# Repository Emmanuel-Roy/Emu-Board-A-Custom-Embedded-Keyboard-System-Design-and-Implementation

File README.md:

# Emu-Board: A Custom Embedded Keyboard System Design and Implementation
A Custom Keyboard Designed *Almost Entirely From Scratch.

Images:

Things Designed From Scratch

  -PCB (Using KiCad and ScottoKeebs Footprint and Symbol Libraries)

  -Casing (Using Ruby to laser cut the acrylic)

  -Keyboard Matrix Firmware Code (Using KMK Firmware to do the majority of the processing.)

Components Bought:

  -77 Key Switches (Boba U4T)

  -77 1N4148 Diodes

  -Durock Plate Mounted Stabilizers

  -Raspberry Pi Pico

  -Keycaps

  -M.2 Screws and Standoffs

I used the following resources to help with this project.

  -https://matt3o.com/anatomy-of-a-keyboard/

  -http://www.keyboard-layout-editor.com/

  -http://builder.swillkb.com/

  -https://github.com/joe-scotto/scottokeebs/tree/main/Extras/ScottoKicad

  -https://www.youtube.com/watch?v=8WXpGTIbxlQ

  -https://www.youtube.com/watch?v=8WXpGTIbxlQ

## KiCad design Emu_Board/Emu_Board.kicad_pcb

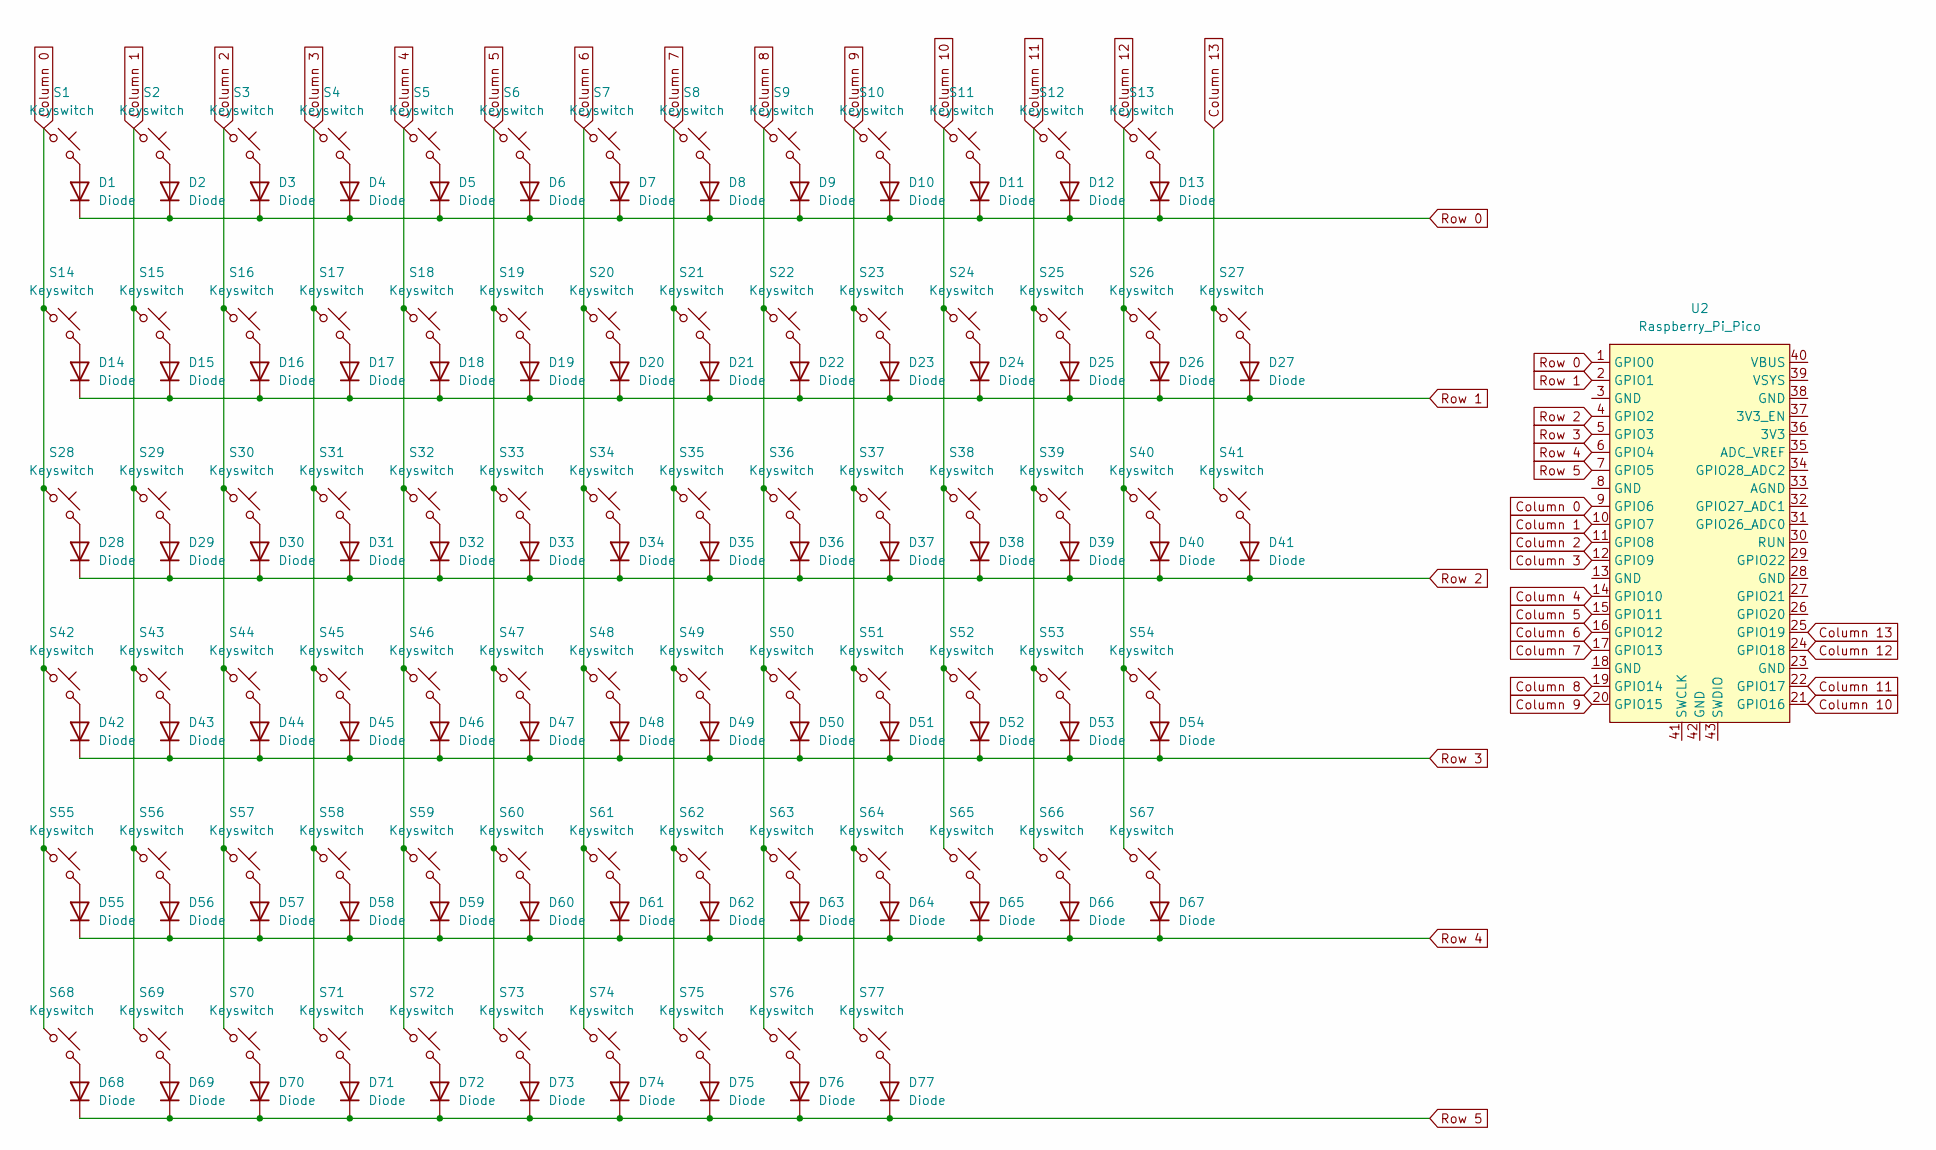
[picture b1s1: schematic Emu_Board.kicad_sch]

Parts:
D1, D2, D3, D4, D5, D6, D7, D8, D9, D10, D11, D12, D13, D14, D15, D16, D17, D18, D19, D20, D21, D22, D23, D24, D25, D26, D27, D28, D29, D30, D31, D32, D33, D34, D35, D36, D37, D38, D39, D40, D41, D42, D43, D44, D45, D46, D47, D48, D49, D50, D51, D52, D53, D54, D55, D56, D57, D58, D59, D60, D61, D62, D63, D64, D65, D66, D67, D68, D69, D70, D71, D72, D73, D74, D75, D76, D77: Diode; Diode_DO-35
S1, S2, S3, S4, S5, S6, S7, S8, S9, S10, S11, S12, S13, S14, S15, S16, S17, S18, S19, S20, S21, S22, S23, S24, S25, S26, S29, S30, S31, S32, S33, S34, S35, S36, S37, S38, S39, S40, S43, S44, S45, S46, S47, S48, S49, S50, S51, S52, S53, S56, S57, S58, S59, S60, S61, S62, S63, S64, S65, S67, S75, S76, S77: Keyswitch; MX_PCB_1.00u
S27: Keyswitch; MX_PCB_2.00u
S28, S41: Keyswitch; MX_PCB_1.50u
S42: Keyswitch; MX_PCB_1.75u
S54, S55: Keyswitch; MX_PCB_2.25u
S66: Keyswitch; MX_PCB_2.75u
S68, S69, S70, S72, S73, S74: Keyswitch; MX_PCB_1.25u
S71: Keyswitch; MX_PCB_6.25u
U2: Raspberry_Pi_Pico

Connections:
Column 0: S1.1, S14.1, S28.1, S42.1, S55.1, S68.1, U2.9 (GPIO6)
Column 1: S2.1, S15.1, S29.1, S43.1, S56.1, S69.1, U2.10 (GPIO7)
Column 2: S3.1, S16.1, S30.1, S44.1, S57.1, S70.1, U2.11 (GPIO8)
Column 3: S4.1, S17.1, S31.1, S45.1, S58.1, S71.1, U2.12 (GPIO9)
Column 4: S5.1, S18.1, S32.1, S46.1, S59.1, S72.1, U2.14 (GPIO10)
Column 5: S6.1, S19.1, S33.1, S47.1, S60.1, S73.1, U2.15 (GPIO11)
Column 6: S7.1, S20.1, S34.1, S48.1, S61.1, S74.1, U2.16 (GPIO12)
Column 7: S8.1, S21.1, S35.1, S49.1, S62.1, S75.1, U2.17 (GPIO13)
Column 8: S9.1, S22.1, S36.1, S50.1, S63.1, S76.1, U2.19 (GPIO14)
Column 9: S10.1, S23.1, S37.1, S51.1, S64.1, S77.1, U2.20 (GPIO15)
Column 10: S11.1, S24.1, S38.1, S52.1, S65.1, U2.21 (GPIO16)
Column 11: S12.1, S25.1, S39.1, S53.1, S66.1, U2.22 (GPIO17)
Column 12: S13.1, S26.1, S40.1, S54.1, S67.1, U2.24 (GPIO18)
Column 13: S27.1, S41.1, U2.25 (GPIO19)
unnamed: D1.2 (A), S1.2
unnamed: D2.2 (A), S2.2
unnamed: D3.2 (A), S3.2
unnamed: D4.2 (A), S4.2
unnamed: D5.2 (A), S5.2
unnamed: D6.2 (A), S6.2
unnamed: D7.2 (A), S7.2
unnamed: D8.2 (A), S8.2
unnamed: D9.2 (A), S9.2
unnamed: D10.2 (A), S10.2
unnamed: D11.2 (A), S11.2
unnamed: D12.2 (A), S12.2
unnamed: D13.2 (A), S13.2
unnamed: D14.2 (A), S14.2
unnamed: D15.2 (A), S15.2
unnamed: D16.2 (A), S16.2
unnamed: D17.2 (A), S17.2
unnamed: D18.2 (A), S18.2
unnamed: D19.2 (A), S19.2
unnamed: D20.2 (A), S20.2
unnamed: D21.2 (A), S21.2
unnamed: D22.2 (A), S22.2
unnamed: D23.2 (A), S23.2
unnamed: D24.2 (A), S24.2
unnamed: D25.2 (A), S25.2
unnamed: D26.2 (A), S26.2
unnamed: D27.2 (A), S27.2
unnamed: D28.2 (A), S28.2
unnamed: D29.2 (A), S29.2
unnamed: D30.2 (A), S30.2
unnamed: D31.2 (A), S31.2
unnamed: D32.2 (A), S32.2
unnamed: D33.2 (A), S33.2
unnamed: D34.2 (A), S34.2
unnamed: D35.2 (A), S35.2
unnamed: D36.2 (A), S36.2
unnamed: D37.2 (A), S37.2
unnamed: D38.2 (A), S38.2
unnamed: D39.2 (A), S39.2
unnamed: D40.2 (A), S40.2
unnamed: D41.2 (A), S41.2
unnamed: D42.2 (A), S42.2
unnamed: D43.2 (A), S43.2
unnamed: D44.2 (A), S44.2
unnamed: D45.2 (A), S45.2
unnamed: D46.2 (A), S46.2
unnamed: D47.2 (A), S47.2
unnamed: D48.2 (A), S48.2
unnamed: D49.2 (A), S49.2
unnamed: D50.2 (A), S50.2
unnamed: D51.2 (A), S51.2
unnamed: D52.2 (A), S52.2
unnamed: D53.2 (A), S53.2
unnamed: D54.2 (A), S54.2
unnamed: D55.2 (A), S55.2
unnamed: D56.2 (A), S56.2
unnamed: D57.2 (A), S57.2
unnamed: D58.2 (A), S58.2
unnamed: D59.2 (A), S59.2
unnamed: D60.2 (A), S60.2
unnamed: D61.2 (A), S61.2
unnamed: D62.2 (A), S62.2
unnamed: D63.2 (A), S63.2
unnamed: D64.2 (A), S64.2
unnamed: D65.2 (A), S65.2
unnamed: D66.2 (A), S66.2
unnamed: D67.2 (A), S67.2
unnamed: D68.2 (A), S68.2
unnamed: D69.2 (A), S69.2
unnamed: D70.2 (A), S70.2
unnamed: D71.2 (A), S71.2
unnamed: D72.2 (A), S72.2
unnamed: D73.2 (A), S73.2
unnamed: D74.2 (A), S74.2
unnamed: D75.2 (A), S75.2
unnamed: D76.2 (A), S76.2
unnamed: D77.2 (A), S77.2
Row 0: D1.1 (K), D2.1 (K), D3.1 (K), D4.1 (K), D5.1 (K), D6.1 (K), D7.1 (K), D8.1 (K), D9.1 (K), D10.1 (K), D11.1 (K), D12.1 (K), D13.1 (K), U2.1 (GPIO0)
Row 1: D14.1 (K), D15.1 (K), D16.1 (K), D17.1 (K), D18.1 (K), D19.1 (K), D20.1 (K), D21.1 (K), D22.1 (K), D23.1 (K), D24.1 (K), D25.1 (K), D26.1 (K), D27.1 (K), U2.2 (GPIO1)
Row 2: D28.1 (K), D29.1 (K), D30.1 (K), D31.1 (K), D32.1 (K), D33.1 (K), D34.1 (K), D35.1 (K), D36.1 (K), D37.1 (K), D38.1 (K), D39.1 (K), D40.1 (K), D41.1 (K), U2.4 (GPIO2)
Row 3: D42.1 (K), D43.1 (K), D44.1 (K), D45.1 (K), D46.1 (K), D47.1 (K), D48.1 (K), D49.1 (K), D50.1 (K), D51.1 (K), D52.1 (K), D53.1 (K), D54.1 (K), U2.5 (GPIO3)
Row 4: D55.1 (K), D56.1 (K), D57.1 (K), D58.1 (K), D59.1 (K), D60.1 (K), D61.1 (K), D62.1 (K), D63.1 (K), D64.1 (K), D65.1 (K), D66.1 (K), D67.1 (K), U2.6 (GPIO4)
Row 5: D68.1 (K), D69.1 (K), D70.1 (K), D71.1 (K), D72.1 (K), D73.1 (K), D74.1 (K), D75.1 (K), D76.1 (K), D77.1 (K), U2.7 (GPIO5)

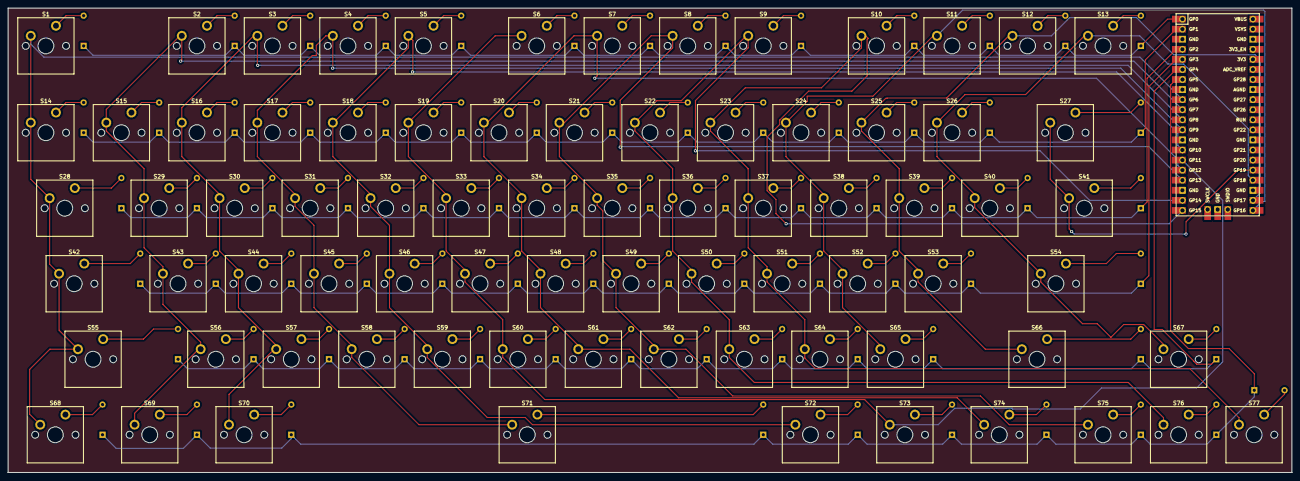
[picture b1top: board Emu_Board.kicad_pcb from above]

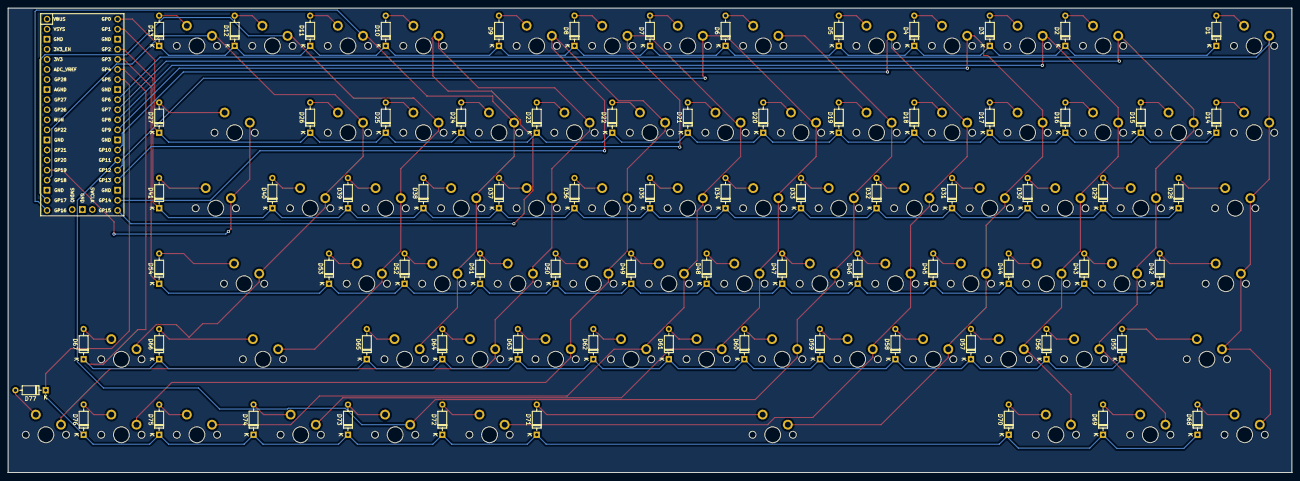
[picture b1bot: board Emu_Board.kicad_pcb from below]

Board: 2 copper layers, 323.8 x 117.2 mm, 155 parts (77 on the bottom side), 97 nets.

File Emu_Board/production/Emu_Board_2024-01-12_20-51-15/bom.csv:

Designator,Footprint,Quantity,Value,LCSC Part #
"D1, D10, D11, D12, D13, D14, D15, D16, D17, D18, D19, D2, D20, D21, D22, D23, D24, D25, D26, D27, D28, D29, D3, D30, D31, D32, D33, D34, D35, D36, D37, D38, D39, D4, D40, D41, D42, D43, D44, D45, D46, D47, D48, D49, D5, D50, D51, D52, D53, D54, D55, D56, D57, D58, D59, D6, D60, D61, D62, D63, D64, D65, D66, D67, D68, D69, D7, D70, D71, D72, D73, D74, D75, D76, D77, D8, D9",Diode_DO-35,77,Diode,
"S1, S10, S11, S12, S13, S14, S15, S16, S17, S18, S19, S2, S20, S21, S22, S23, S24, S25, S26, S29, S3, S30, S31, S32, S33, S34, S35, S36, S37, S38, S39, S4, S40, S43, S44, S45, S46, S47, S48, S49, S5, S50, S51, S52, S53, S56, S57, S58, S59, S6, S60, S61, S62, S63, S64, S65, S67, S7, S75, S76, S77, S8, S9",MX_PCB_1.00u,63,Keyswitch,
S27,MX_PCB_2.00u,1,Keyswitch,
"S28, S41",MX_PCB_1.50u,2,Keyswitch,
S42,MX_PCB_1.75u,1,Keyswitch,
"S54, S55",MX_PCB_2.25u,2,Keyswitch,
S66,MX_PCB_2.75u,1,Keyswitch,
"S68, S69, S70, S72, S73, S74",MX_PCB_1.25u,6,Keyswitch,
S71,MX_PCB_6.25u,1,Keyswitch,
U2,Raspberry_Pi_Pico,1,Raspberry_Pi_Pico,
